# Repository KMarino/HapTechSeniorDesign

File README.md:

# HapTechSeniorDesign

#### Install dependencies

        sudo apt-get install build-essential scons cmake freeglut3-dev 

#### Rtaudio
First clone Rtaudio to extern
	cd extern/
	git clone https://github.com/thestk/rtaudio.git
	cd rtaudio
	autoconf
	./configure
	make
#### Aquila

First clone Aqulia to extern

	cd extern/
	git clone git://github.com/zsiciarz/aquila.git aquila-src
	cd ..

Make a build directory for Aquila
Aquila must be built with `cmake`, which doesn't play nice with `make`

        mkdir extern/aquila
	cd aquila
        cmake ../aquila-src
 	
	make
	sudo make install

#### Build Included dependencies

This will build gtest, jsoncpp, and aquila

### Build

        make

#### Run

        ./bin/effects_model_ui config/hardware.json config/mapping.json

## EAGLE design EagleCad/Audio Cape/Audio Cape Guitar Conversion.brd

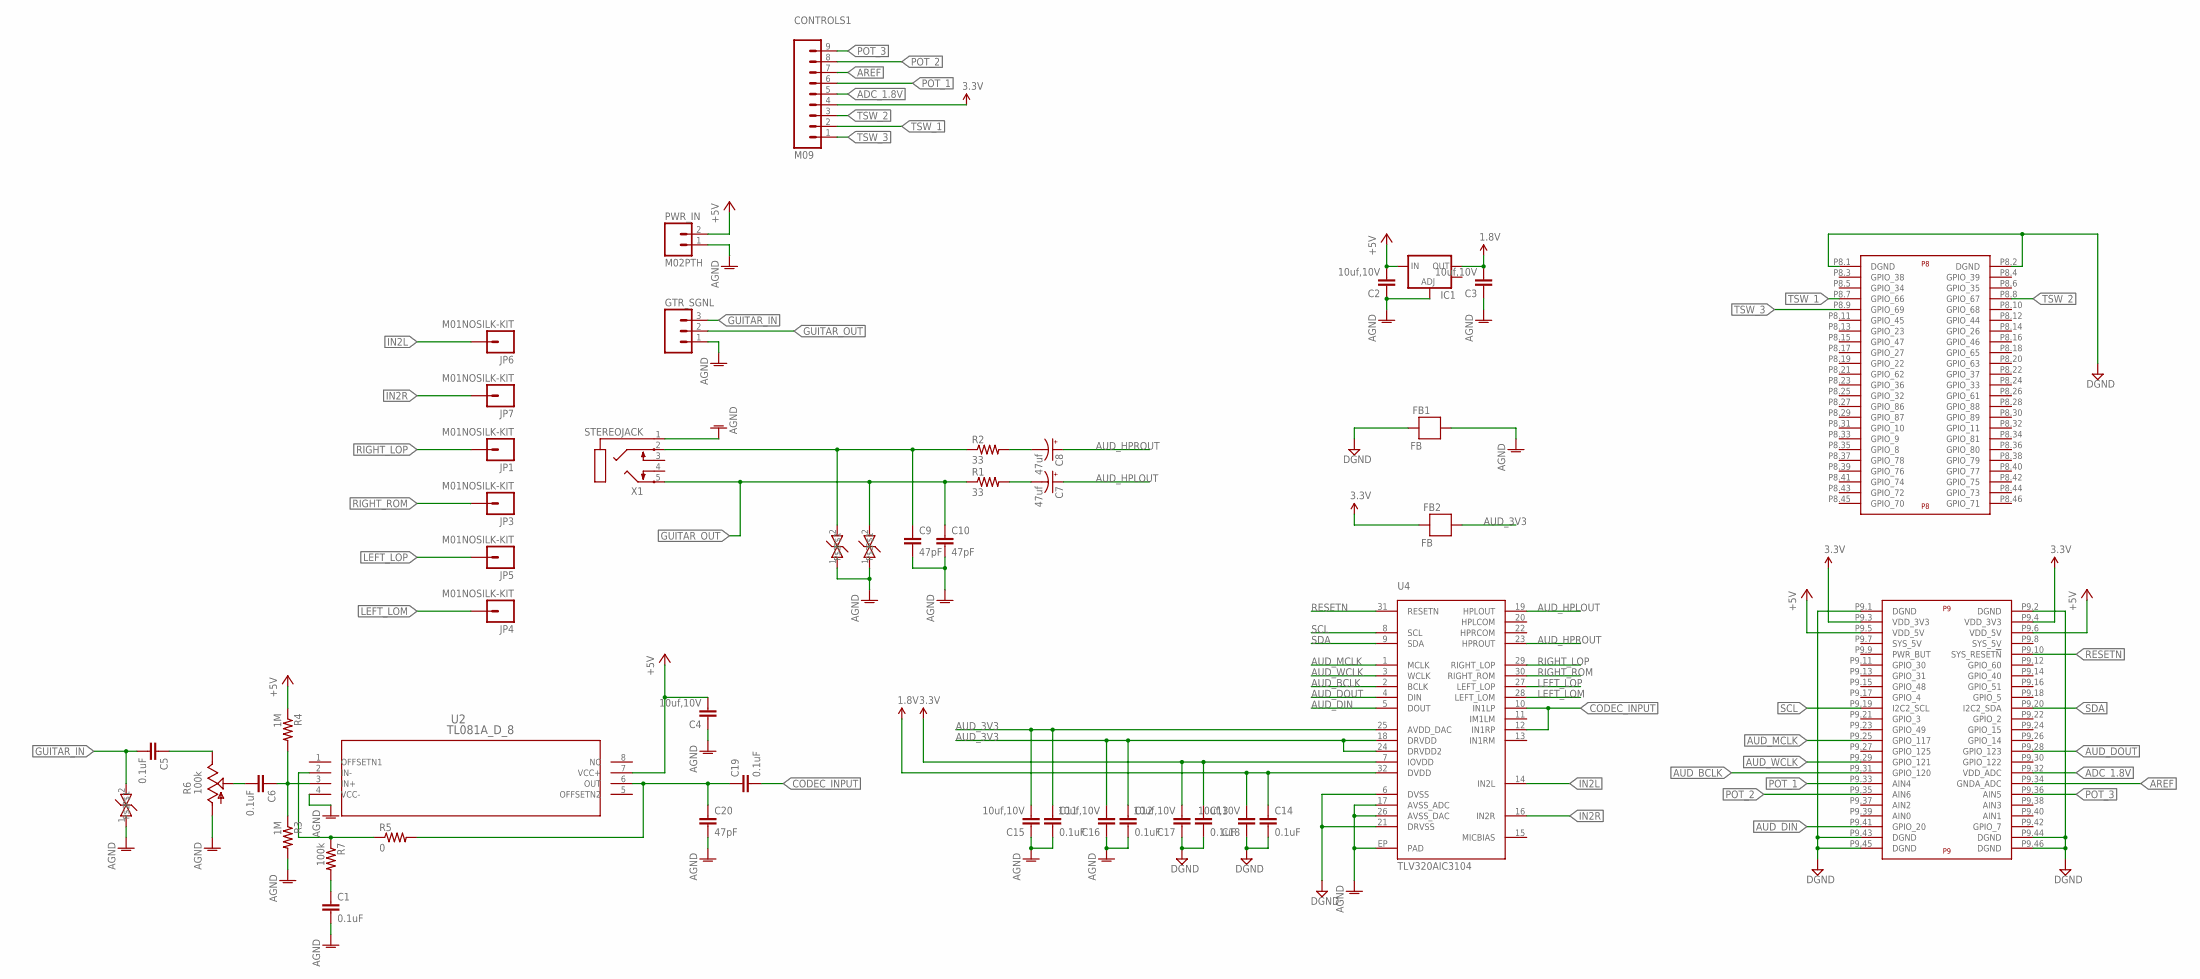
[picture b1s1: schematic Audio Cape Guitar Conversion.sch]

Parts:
C1, C5, C6, C11, C12, C13, C14, C19: 0.1uF; 0603-CAP
C2, C3, C4, C15, C16, C17, C18: 10uf,10V; 0603-CAP
C7, C8: 47uf; EIA3216
C9, C10, C20: 47pF; 0402-CAP
CONTROLS1: M09; 1X09
D1, D2, D3: PGB0010603MR; 0603
FB1, FB2: FB; 0603
GTR_SGNL: M03PTH; 1X03
IC1: V_REG_LM1117SOT223; SOT223
JP1, JP3, JP4, JP5, JP6, JP7: M01NOSILK-KIT; 1X01NS-KIT
PWR_IN: M02PTH; 1X02
R1, R2: 33; 1206
R3, R4: 1M; 1206
R5: 0; AXIAL-0.4
R6: 100k; S64Y
R7: 100k; 1206
U2: TL081A_D_8; D8
U4: TLV320AIC3104; QFN-32
U$1: BEAGLE_BONE_BLACK_CAPE
X1: STEREOJACK; STX3100

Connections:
1.8V: C3.2, C14.1, C18.2, IC1.2 (OUT), U4.32 (DVDD)
3.3V: C13.1, C17.2, CONTROLS1.4, FB2.2, U4.7 (IOVDD), U$1.P9.3 (VDD_3V3), U$1.P9.4 (VDD_3V3)
+5V: C2.2, C4.2, IC1.3 (IN), PWR_IN.2, R4.1, U2.7 (VCC+), U$1.P9.5 (VDD_5V), U$1.P9.6 (VDD_5V)
ADC_1.8V: CONTROLS1.5, U$1.P9.32 (VDD_ADC)
AGND: C1.2, C2.1, C3.1, C4.1, C9.2, C10.2, C11.2, C12.2, C15.1, C16.1, C20.2, D1.1, D2.1, D3.1, FB1.1, GTR_SGNL.1, IC1.1 (ADJ), PWR_IN.1, R3.2, R6.A, U2.4 (VCC-), U4.17 (AVSS_ADC), U4.26 (AVSS_DAC), U4.EP (PAD), X1.1
AREF: CONTROLS1.7, U$1.P9.34 (GNDA_ADC)
AUD_3V3: C11.1, C12.1, C15.2, C16.2, FB2.1, U4.18 (DRVDD), U4.24 (DRVDD2), U4.25 (AVDD_DAC)
AUD_BCLK: U4.2 (BCLK), U$1.P9.31 (GPIO_120)
AUD_DIN: U4.5 (DOUT), U$1.P9.41 (GPIO_20)
AUD_DOUT: U4.4 (DIN), U$1.P9.28 (GPIO_123)
AUD_HPLOUT: C7.A (+), U4.19 (HPLOUT)
AUD_HPROUT: C8.A (+), U4.23 (HPROUT)
AUD_MCLK: U4.1 (MCLK), U$1.P9.25 (GPIO_117)
AUD_WCLK: U4.3 (WCLK), U$1.P9.29 (GPIO_121)
CODEC_INPUT: C19.2, U4.10 (IN1LP), U4.12 (IN1RP)
DGND: C13.2, C14.2, C17.1, C18.1, FB1.2, U4.6 (DVSS), U4.21 (DRVSS), U$1.P8.1 (DGND), U$1.P8.2 (DGND), U$1.P9.1 (DGND), U$1.P9.2 (DGND), U$1.P9.43 (DGND), U$1.P9.44 (DGND), U$1.P9.45 (DGND), U$1.P9.46 (DGND)
GUITAR_IN: C5.2, D3.2, GTR_SGNL.3
GUITAR_OUT: C10.1, D2.2, GTR_SGNL.2, R1.1, X1.5
IN2L: JP6.1, U4.14 (IN2L)
IN2R: JP7.1, U4.16 (IN2R)
LEFT_LOM: JP4.1, U4.28 (LEFT_LOM)
LEFT_LOP: JP5.1, U4.27 (LEFT_LOP)
unnamed: C7.C (-), R1.2
unnamed: C5.1, R6.E
unnamed: C6.1, R3.1, R4.2, U2.3 (IN+)
unnamed: C1.1, R7.2
unnamed: C8.C (-), R2.2
unnamed: R5.P$1 (1), R7.1, U2.2 (IN-)
unnamed: C19.1, C20.1, R5.P$2 (2), U2.6 (OUT)
unnamed: C6.2, R6.S
OUTR: C9.1, D1.2, R2.1, X1.2
POT_1: CONTROLS1.6, U$1.P9.33 (AIN4)
POT_2: CONTROLS1.8, U$1.P9.35 (AIN6)
POT_3: CONTROLS1.9, U$1.P9.36 (AIN5)
RESETN: U4.31 (RESETN), U$1.P9.10 (SYS_RESET!N)
RIGHT_LOP: JP1.1, U4.29 (RIGHT_LOP)
RIGHT_ROM: JP3.1, U4.30 (RIGHT_ROM)
SCL: U4.8 (SCL), U$1.P9.19 (I2C2_SCL)
SDA: U4.9 (SDA), U$1.P9.20 (I2C2_SDA)
TSW_1: CONTROLS1.2, U$1.P8.7 (GPIO_66)
TSW_2: CONTROLS1.3, U$1.P8.8 (GPIO_67)
TSW_3: CONTROLS1.1, U$1.P8.9 (GPIO_69)

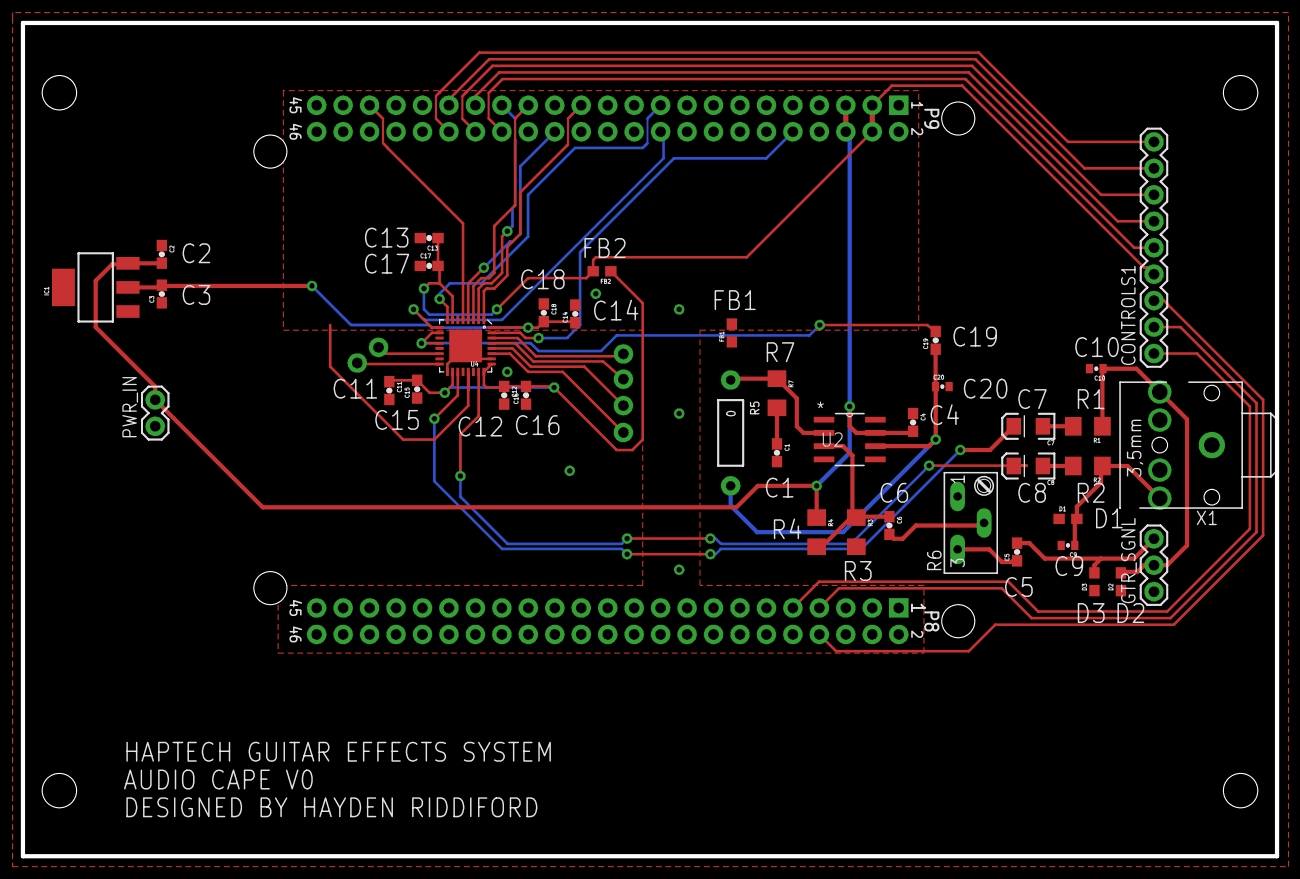
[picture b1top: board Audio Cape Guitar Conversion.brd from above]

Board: 2 copper layers, 120.4 x 80.0 mm, 46 parts (0 on the bottom side), 42 nets.

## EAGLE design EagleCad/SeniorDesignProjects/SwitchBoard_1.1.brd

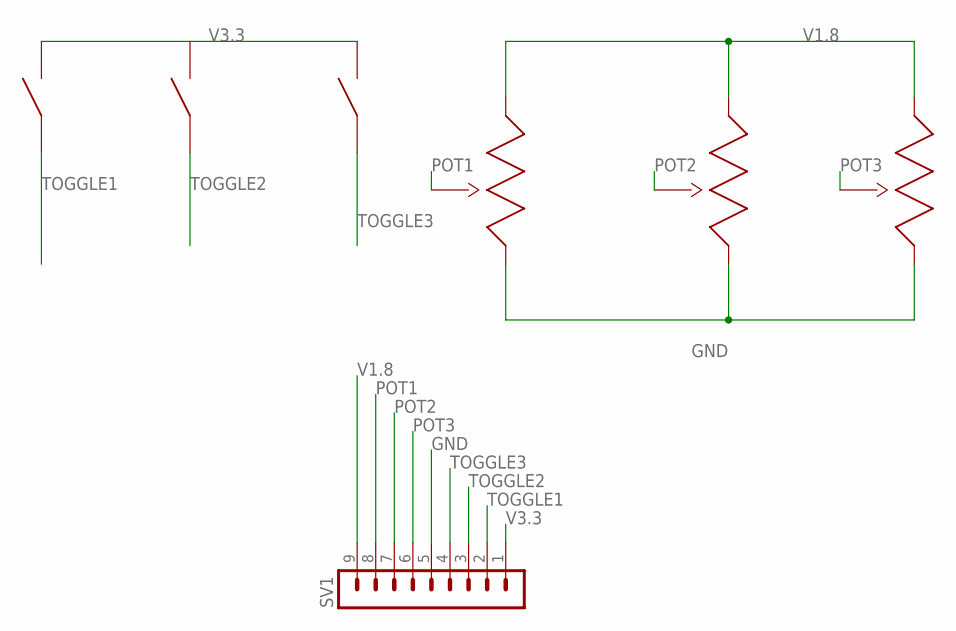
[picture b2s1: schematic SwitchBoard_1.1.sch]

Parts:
POT1, POT2, POT3: PRS11S-11; POT-SMD
SV1: MA09-1
TOGGLE1, TOGGLE2, TOGGLE3: COM-09276; SPST-TOGGLE-SWITCH

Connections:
GND: POT1.1, POT2.1, POT3.1, SV1.5
POT1: POT1.2, SV1.8
POT2: POT2.2, SV1.7
POT3: POT3.2, SV1.6
TOGGLE1: SV1.2, TOGGLE1.1
TOGGLE2: SV1.3, TOGGLE2.1
TOGGLE3: SV1.4, TOGGLE3.1
V1.8: POT1.3, POT2.3, POT3.3, SV1.9
V3.3: SV1.1, TOGGLE1.2, TOGGLE2.2, TOGGLE3.2

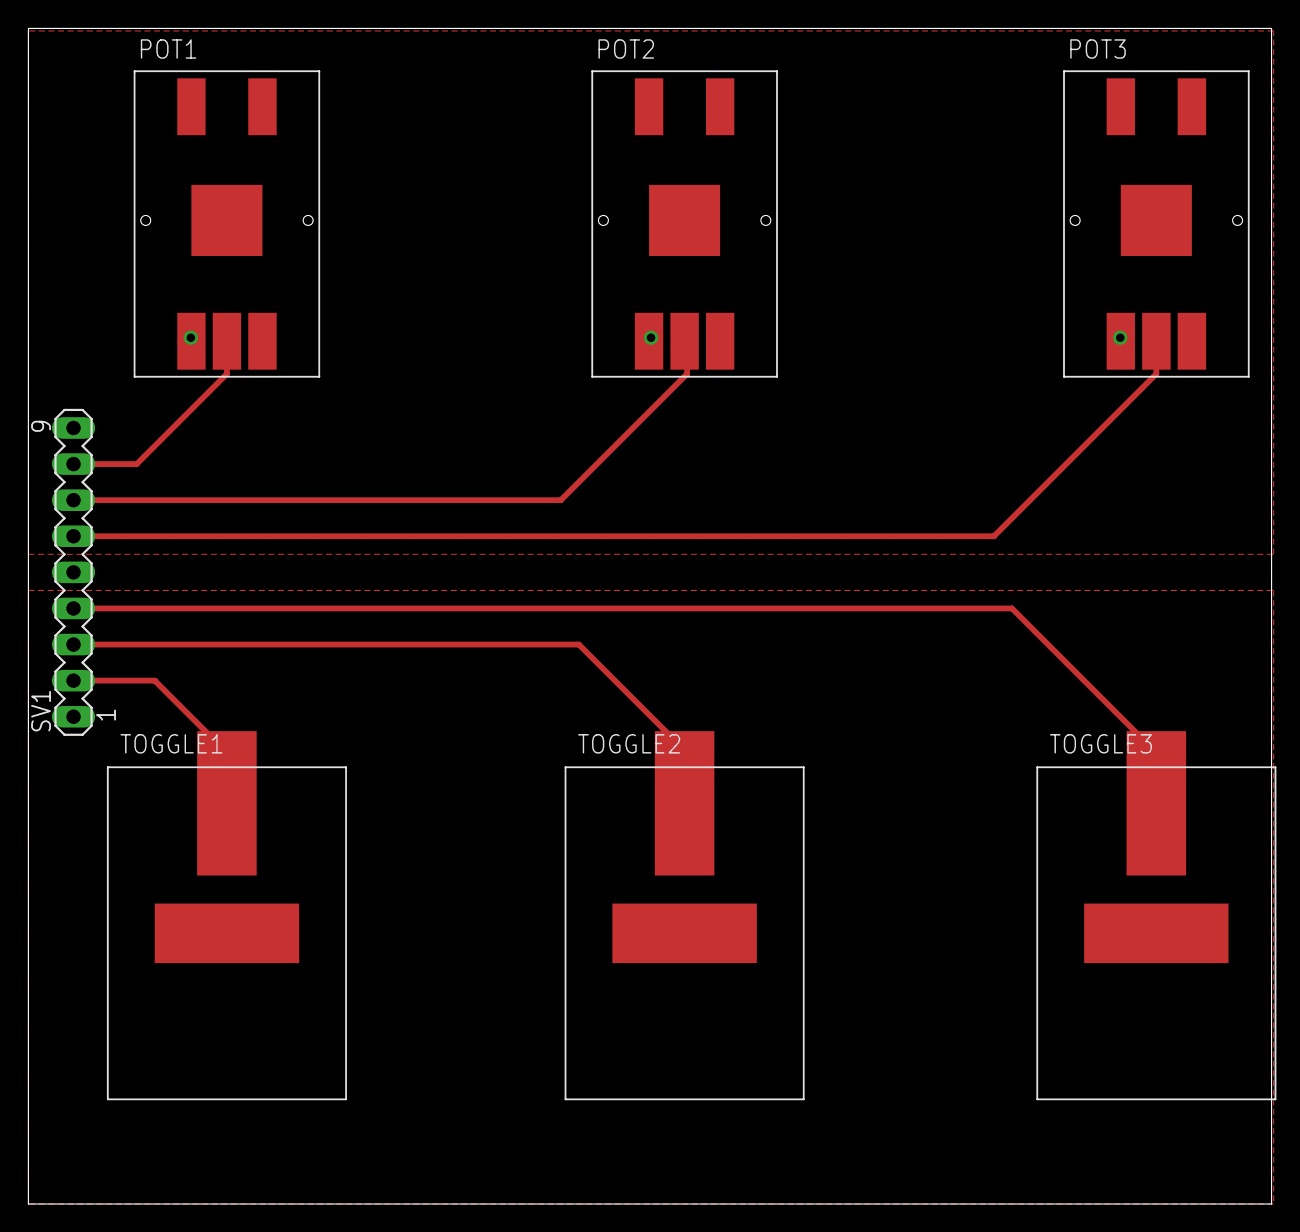
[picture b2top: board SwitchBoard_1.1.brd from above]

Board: 2 copper layers, 87.5 x 82.7 mm, 7 parts (0 on the bottom side), 9 nets.

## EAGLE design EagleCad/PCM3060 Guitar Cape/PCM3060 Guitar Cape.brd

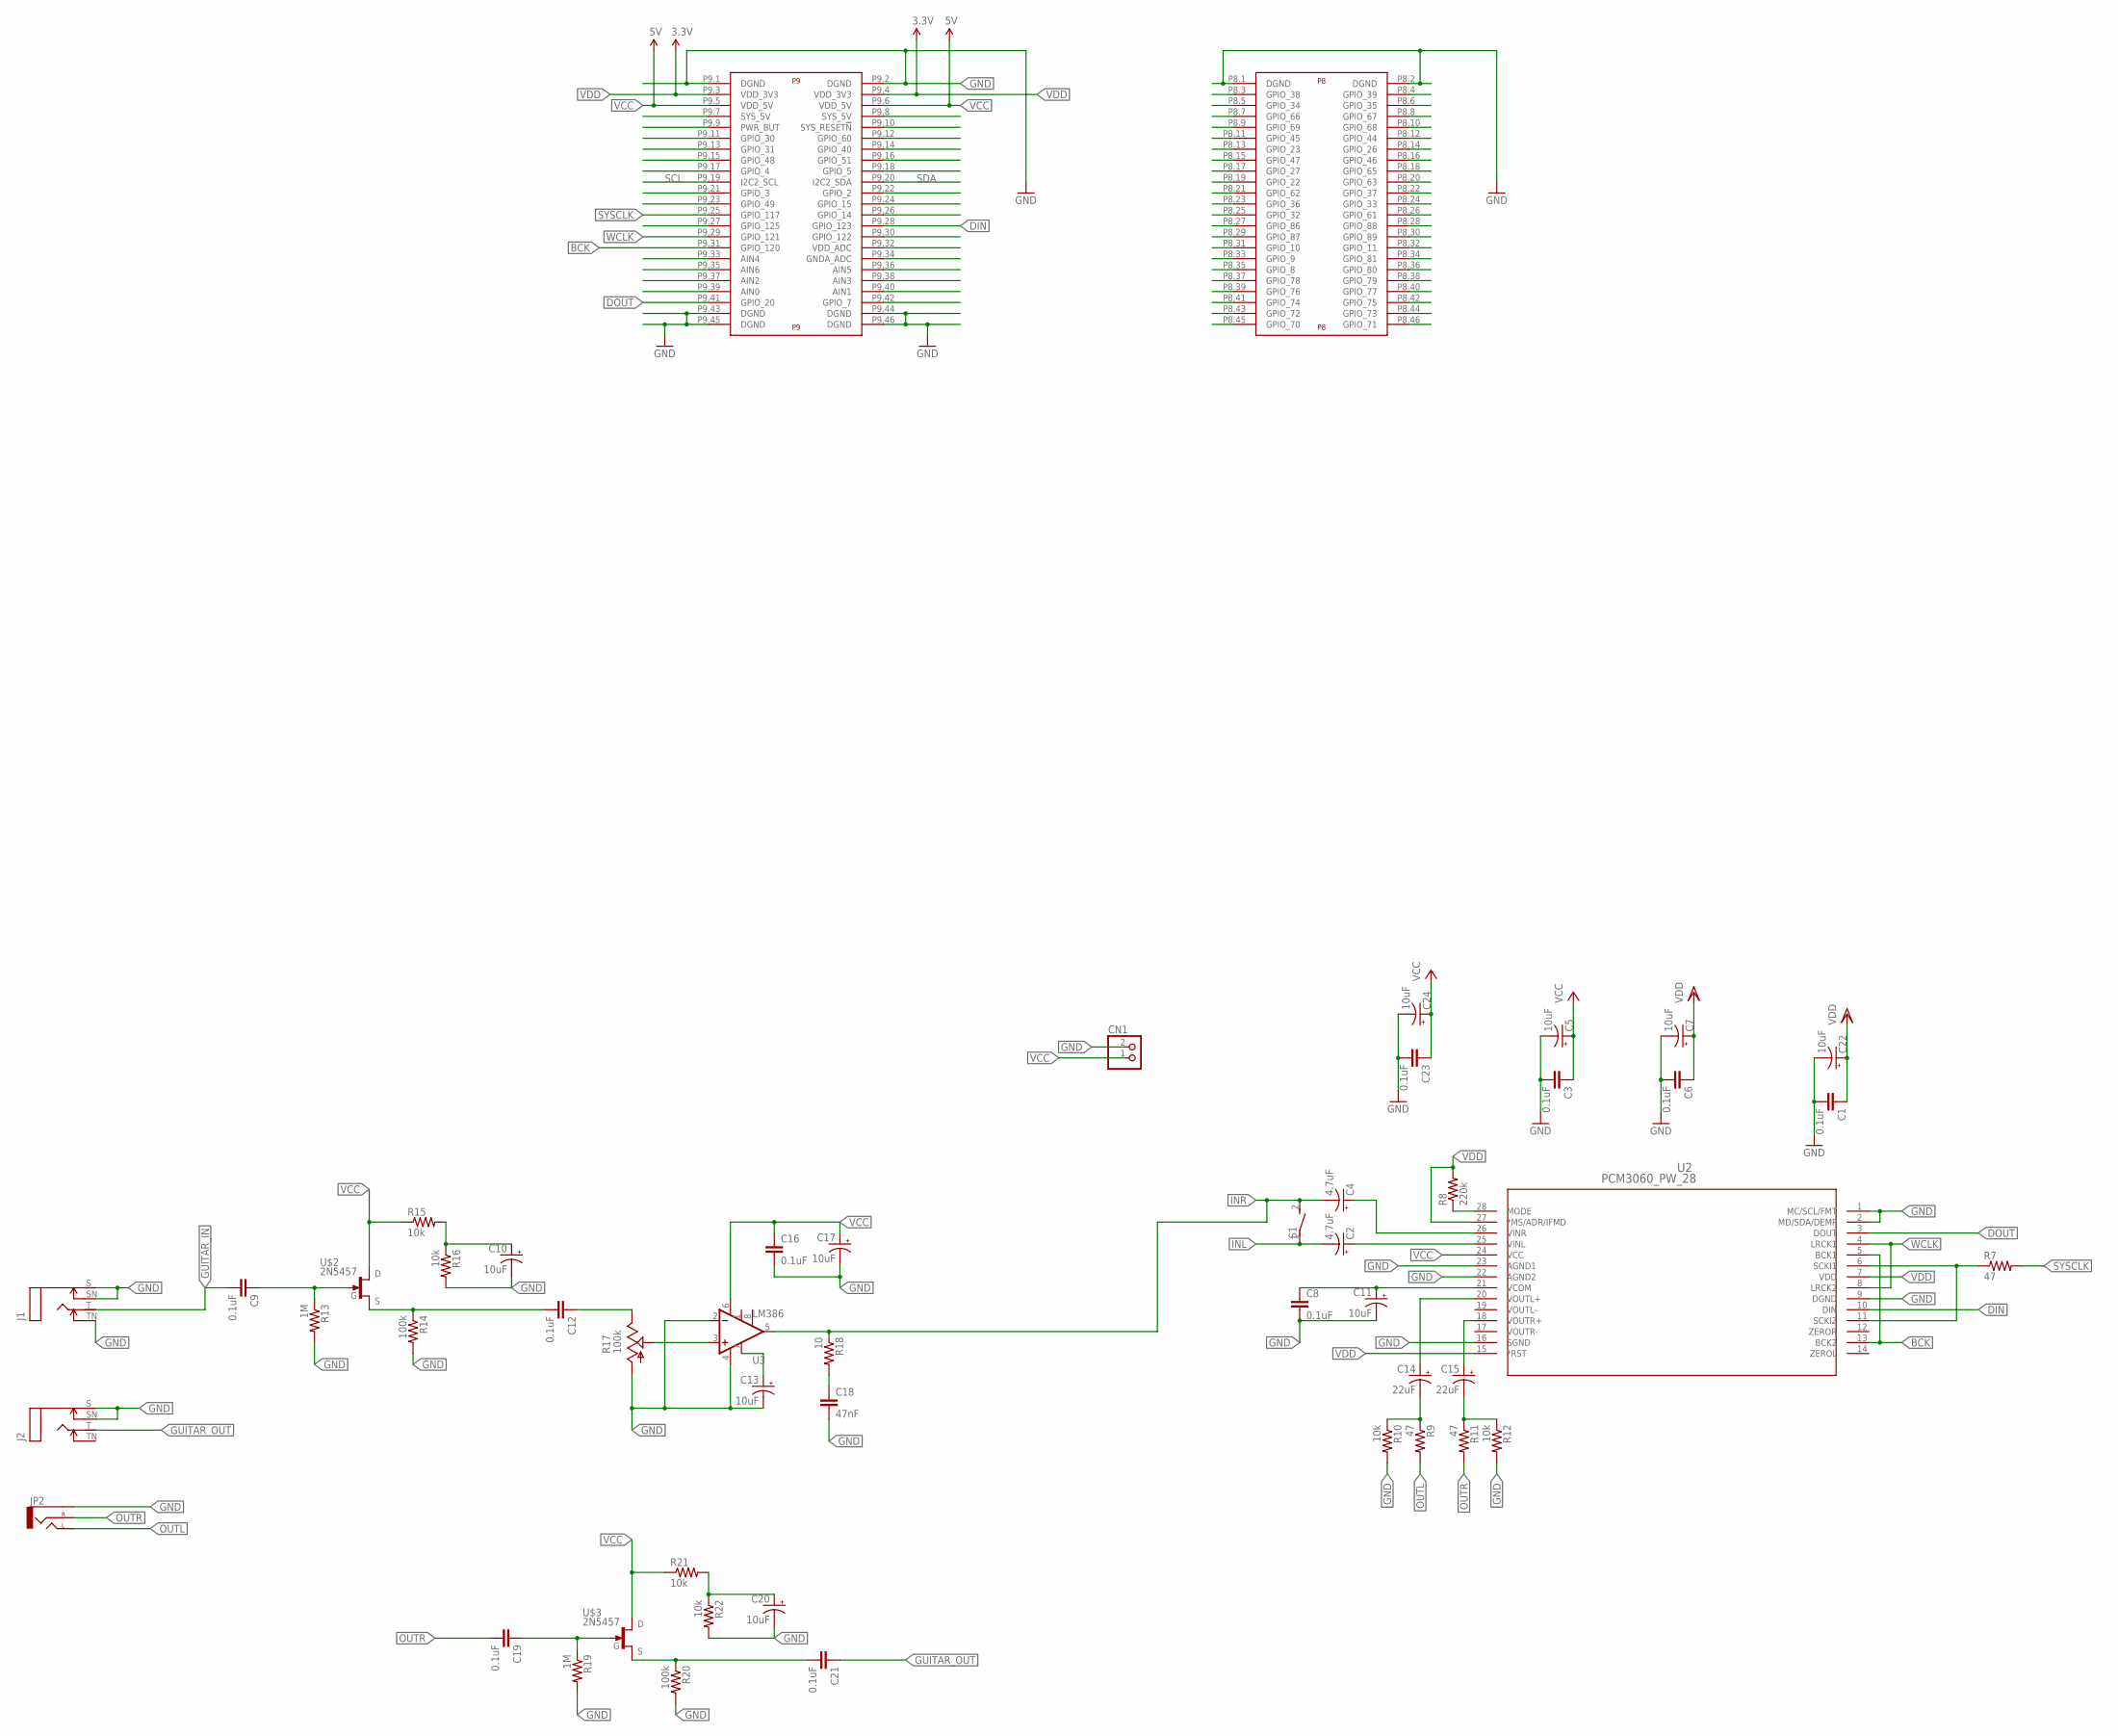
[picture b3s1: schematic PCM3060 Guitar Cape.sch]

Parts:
C1, C3, C6, C8, C9, C12, C16, C19, C21, C23: 0.1uF; 0603-CAP
C2, C4: 4.7uF; CPOL-RADIAL-10UF-25V
C5, C7, C10, C11, C13, C17, C20, C22, C24: 10uF; CPOL-RADIAL-10UF-25V
C14, C15: 22uF; CPOL-RADIAL-10UF-25V
C18: 47nF; 0603-CAP
CN1: JST_2PIN-THM; JST-PH-2-THM
J1, J2: MONOSW; NMJ4HCD2
JP2: AUDIO-JACK2.5MM; STEREOJACK2.5MM_STEREOJACK2.5MM
R7, R9, R11: 47; 1206
R8: 220k; 1206
R10, R12, R15, R16, R21, R22: 10k; 1206
R13, R19: 1M; 1206
R14, R20: 100k; 1206
R17: 100k; RJ9W
R18: 10; 1206
S1: DS01E; DS-01
U2: PCM3060_PW_28; PW28
U3: LM386; DIP08
U$1: BEAGLE_BONE_BLACK_CAPE
U$2, U$3: 2N5457; TO-92

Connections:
BCK: U2.5 (BCK1), U2.13 (BCK2), U$1.P9.31 (GPIO_120)
DIN: U2.10 (DIN), U$1.P9.28 (GPIO_123)
DOUT: U2.3 (DOUT), U$1.P9.41 (GPIO_20)
GND: C1.2, C3.2, C5.2 (-), C6.2, C7.2 (-), C8.2, C10.2 (-), C11.2 (-), C13.2 (-), C16.2, C17.2 (-), C18.2, C20.2 (-), C22.2 (-), C23.2, C24.2 (-), CN1.2 (1), J1.S, J1.SN, J1.TN, J2.S, J2.SN, JP2.RING1 (SLEEVE), R10.2, R12.2, R13.2, R14.2, R16.2, R17.A, R19.2, R20.2, R22.2, U2.1 (MC/SCL/FMT), U2.2 (MD/SDA/DEMP), U2.9 (DGND), U2.16 (SGND), U2.22 (AGND2), U2.23 (AGND1), U3.2 (-IN), U3.4 (V-), U$1.P8.1 (DGND), U$1.P8.2 (DGND), U$1.P9.1 (DGND), U$1.P9.2 (DGND), U$1.P9.43 (DGND), U$1.P9.44 (DGND), U$1.P9.45 (DGND), U$1.P9.46 (DGND)
GUITAR_IN: C9.2, J1.T
GUITAR_OUT: C21.1, J2.T
INL: C2.2 (-), S1.1
INR: C4.2 (-), R18.1, S1.2, U3.5 (OUT)
unnamed: C2.1 (+), U2.25 (VINL)
unnamed: R7.1, U2.6 (SCKI1), U2.11 (SCKI2)
unnamed: C8.1, C11.1 (+), U2.21 (VCOM)
unnamed: R8.1, U2.28 (MODE)
unnamed: C4.1 (+), U2.26 (VINR)
unnamed: C14.1 (+), U2.20 (VOUTL+)
unnamed: C15.1 (+), U2.18 (VOUTR+)
unnamed: C14.2 (-), R9.1, R10.1
unnamed: C15.2 (-), R11.1, R12.1
unnamed: C9.1, R13.1, U$2.3 (G)
unnamed: C12.2, R14.1, U$2.2 (S)
unnamed: C10.1 (+), R15.2, R16.1
unnamed: R17.S, U3.3 (+IN)
unnamed: C13.1 (+), U3.7 (BP)
unnamed: C18.1, R18.2
unnamed: C12.1, R17.E
unnamed: C19.1, R19.1, U$3.3 (G)
unnamed: C21.2, R20.1, U$3.2 (S)
unnamed: C20.1 (+), R21.2, R22.1
OUTL: JP2.SHIELD (LEFT), R9.2
OUTR: C19.2, JP2.TIP (RIGHT), R11.2
SCL: U$1.P9.19 (I2C2_SCL)
SDA: U$1.P9.20 (I2C2_SDA)
SYSCLK: R7.2, U$1.P9.25 (GPIO_117)
VCC: C3.1, C5.1 (+), C16.1, C17.1 (+), C23.1, C24.1 (+), CN1.1 (2), R15.1, R21.1, U2.24 (VCC), U3.6 (V+), U$1.P9.5 (VDD_5V), U$1.P9.6 (VDD_5V), U$2.1 (D), U$3.1 (D)
VDD: C1.1, C6.1, C7.1 (+), C22.1 (+), R8.2, U2.7 (VDD), U2.15 (*RST), U2.27 (*MS/ADR/IFMD), U$1.P9.3 (VDD_3V3), U$1.P9.4 (VDD_3V3)
WCLK: U2.4 (LRCK1), U2.8 (LRCK2), U$1.P9.29 (GPIO_121)

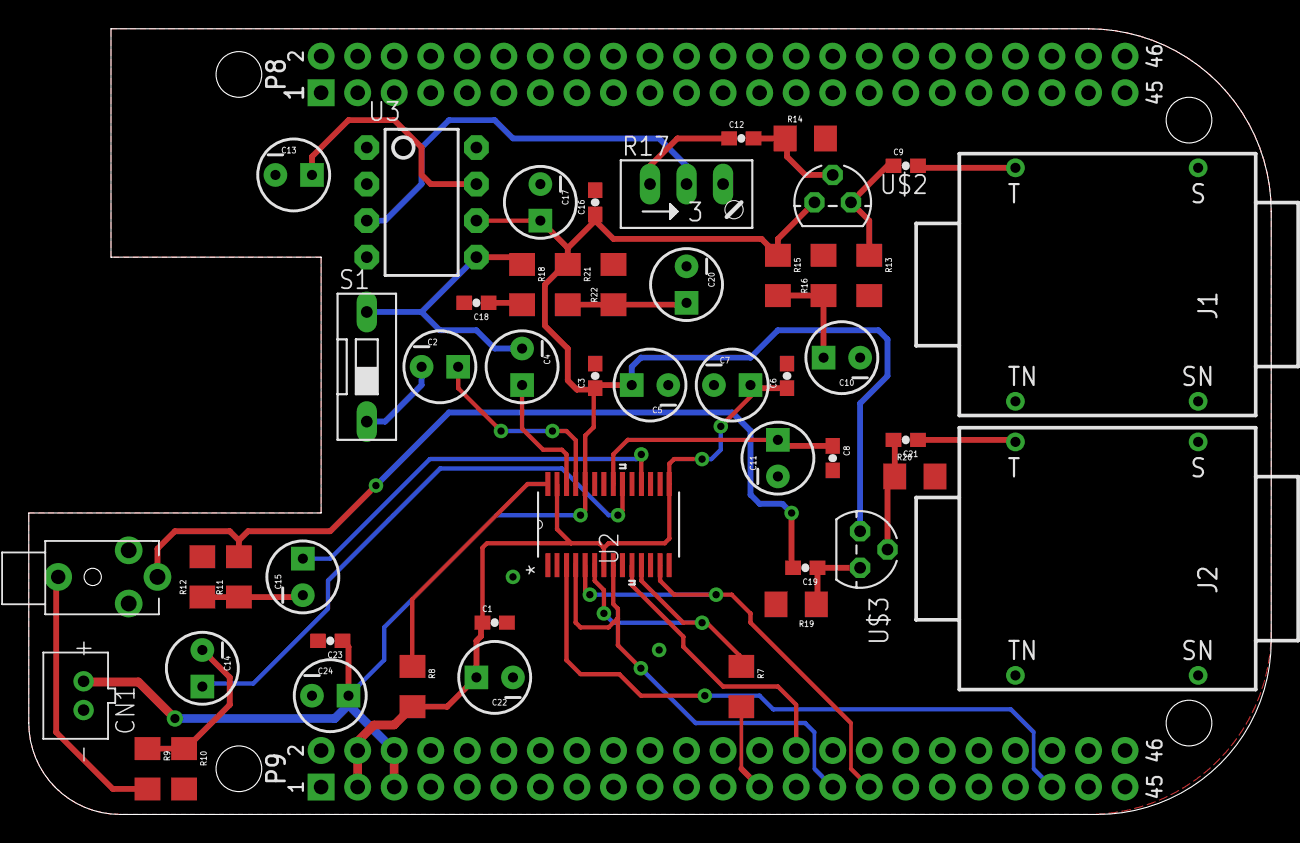
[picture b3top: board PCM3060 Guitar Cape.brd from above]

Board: 2 copper layers, 86.4 x 54.6 mm, 50 parts (0 on the bottom side), 33 nets.

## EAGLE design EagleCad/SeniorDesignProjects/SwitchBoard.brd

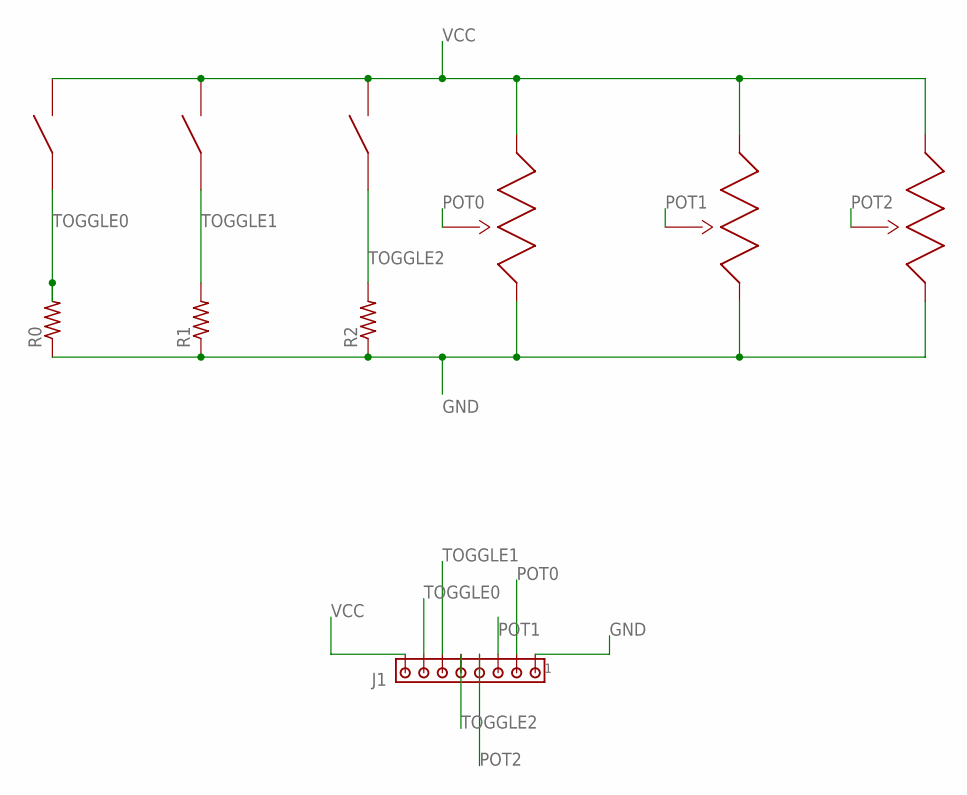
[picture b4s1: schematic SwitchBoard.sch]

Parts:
J1: MTA08-100; 10X08MTA
POT0, POT1, POT2: PRS11S-11; POT-SMD
R0, R1, R2: R-US_0204/5; 0204/5
TOGGLE0, TOGGLE1, TOGGLE2: COM-09276; SPST-TOGGLE-SWITCH

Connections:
GND: J1.1, POT0.1, POT1.1, POT2.1, R0.1, R1.1, R2.1
POT0: J1.2, POT0.2
POT1: J1.3, POT1.2
POT2: J1.4, POT2.2
TOGGLE0: J1.7, R0.2, TOGGLE0.1
TOGGLE1: J1.6, R1.2, TOGGLE1.1
TOGGLE2: J1.5, R2.2, TOGGLE2.1
VCC: J1.8, POT0.3, POT1.3, POT2.3, TOGGLE0.2, TOGGLE1.2, TOGGLE2.2

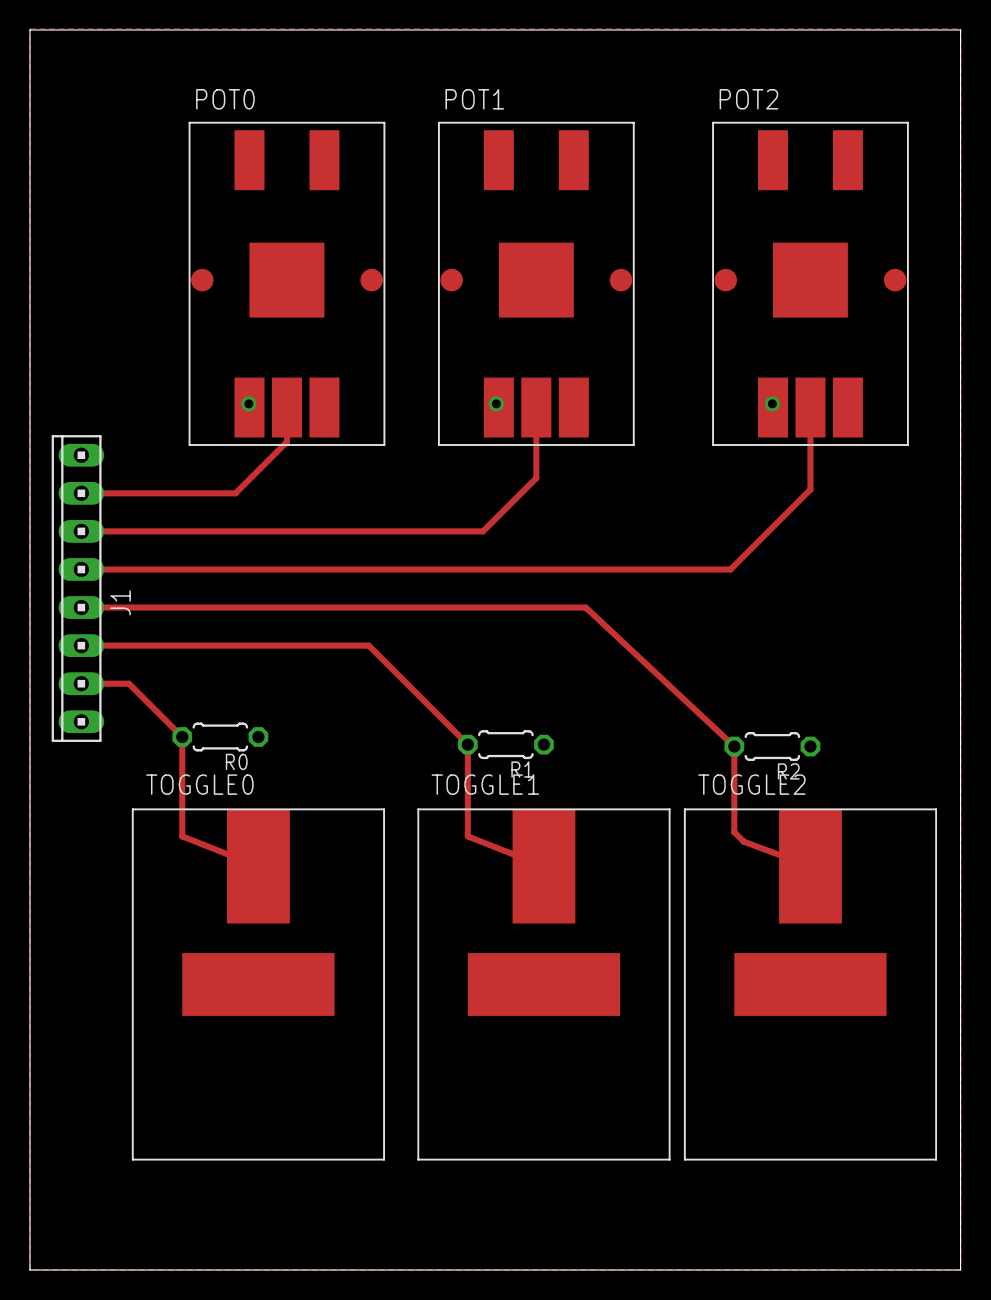
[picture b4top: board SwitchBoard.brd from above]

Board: 2 copper layers, 62.1 x 82.7 mm, 10 parts (0 on the bottom side), 8 nets.

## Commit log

2015-01-11 Initial commit. Set up unittest and json libraries, put help on installing in README, added gitignore, set up Makefile with exaples from last project I did
2015-01-11 Added json file reading basics, code stub for EffectsModel
2015-01-11 Renamed some files, added more class and function stubs, created a main file, updated README to link everything correctly
2015-01-19 Added a bunch fo new classes for effects. Also tested to make sure serialization of effects works correctly
2015-01-20 Added message update stuff. Not sure if it actually is correct yet. Will test this for real, but it doesn't cause a compile issue, so there's that
2015-01-25 Updated README for OpenGL
2015-01-25 Finished serialization functions for messages. Also made unit tests to make sure everything actually works
2015-02-02 Made parsing for hardware config file
2015-02-04 got opengl to display circle on screen
2015-02-11 Fixed hardware state config, reading and storage to be a bit more sensible
2015-02-11 Added linking for opengl to makefile
2015-02-11 Created Folders for EagleCad Libraries, Schematics, and Boards
2015-02-12 Finished Switch Board schematic and Board layout
2015-02-13 Fixed Toggle Switch package for board layout
2015-02-21 Make the dot move
2015-02-22 made the dot move. with the mouse. it's pretty sweet.
2015-02-22 Added code for both config files to be read and interpreted
2015-02-24 PCM3060 Guitar Cape
    Designed a cape to input/output guitar signal according to proposed
    design. May change depending on pending hardware testing.
2015-02-24 Fixed Grounding Issue on Output Jack
    Previously, the switched 1/4" output jack for the system would be
    grounded when no cable was connected. This is correct for the input,
    however grounding the output of the system is not proper.
2015-03-01 Added code to effectsmodel to receive updates from main program, update dial switches and send messages to DSP program. Still needs to actually read the values from pins and actually send messages to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
2015-03-01 Forgot to save a file. Should all be okay now
2015-03-01 Uses eventinfo class, generics
2015-03-01 Flipped x and y. X is now index 0 and Y is index 1, which just makes way more sense
2015-03-01 cleaned up directions
2015-03-01 fixed 'undefined reference to symbol 'pthread_key_delete@@GLIBC_2.2.5' issue
2015-03-01 ignoring some compiled files
2015-03-01 hmmm
2015-03-01 missed some things in the readme
2015-03-01 added EffectsModel and close function
2015-03-01 deleting objects on exit
2015-03-01 Added accessors to EffectUpdateMessage so DSP can actually read what's in it
2015-03-01 added timer func
2015-03-01 Added accessor in EffectsModel to get the screen width and height
2015-03-01 fixed bugs with modelaccess
2015-03-01 added bin dir
2015-03-01 committing broken for Kenny to fix, profile.cpp line 80 count func
2015-03-01 Fixed error in effectsmodel where it doesn't set to value from the wind
2015-03-01 cleaned up effects_model_ui
2015-03-01 aquila things
2015-03-01 updated makefile to use local jsoncpp
2015-03-01 fixed aquila directory
2015-03-01 removed aquila-src
2015-03-01 created module
2015-03-01 added module for real
2015-03-01 fixed for real
2015-03-01 added deps make task
2015-03-01 removed compiled aquila from repo
2015-03-01 some Makefile refactor
2015-03-01 updated to match makefile changes
2015-03-01 clarity
2015-03-06 added working device tree overlay for modded cape
2015-03-06 added test file (30s sweep)
2015-03-09 Updated sch and brd files. Spaced out components, seperated ADC and GPIO power
2015-03-09 minor update the toggle switch footprint to allow for easier soldering
2015-03-10 fixed aquila stuff
2015-03-10 minor fix in readme, fullscreen with q to quit and cutdown events in effects_ui
2015-03-10 fixed duplicate code
2015-03-14 Gitignore merge
2015-03-15 Added a ton of verification. All code should be verified to a reasonable degree except for EffectsModel. That code is hopefully more straightforward. Will be able to write a better unittest for that 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
2015-03-26 cleanup
2015-03-26 added some useful bbb files
2015-03-26 moved some files around
2015-03-26 removed submodule
2015-03-26 fixed aquila paths
2015-03-26 fixed misnamed make task
2015-03-26 updated readme for changes
2015-03-26 made make get-deps task
2015-03-26 updated readme for new task
2015-03-26 added Travis.yml for free CI :)
2015-03-26 removed gitmodules
2015-03-26 wrong file name
2015-03-28 DTOs and scripts to add to beaglebone, basic C functions to read the IO
2015-03-28 Fixed ambgious absolute value call in unittest
2015-03-28 Fixed aquila instructions again
2015-03-28 fixed pthreads bug in Makefile
2015-03-28 Fixed dsp make in Makefile
2015-03-28 fixed unittesting.cpp for 0 test
2015-03-28 fixed formatting
2015-03-29 Added h and cpp files for IPC sockets. not integrated yet
2015-03-29 forgot one
2015-03-29 Fixed stream/dgram errors in socket things. Also minor change in effectsmodel for usability of var
2015-04-03 Audio Cape with Guitar Preamp
    Updated cape that includes the codec for signal conversion, as well as a
    preamp for the guitar input. Headers for power, guitar signal
    input/output, and signals routed to the controls board are also included
    on the board.
2015-04-04 Integrating socket code with minor improvements
2015-04-04 made socket test
2015-04-04 integrating ipc code and test
2015-04-04 Integrated gpio code into main build. Also changed functions slightly so it returns either 0 or 1 or it returns a float voltage value
2015-04-04 pthreads in socket code. doesn't work yet.
2015-04-05 Unreverted a lot of things. Added GPIO back in and fixed the original bug. Should now be able to read from hardware pins
2015-04-05 dsp code, still has threading issues but runs
2015-04-05 Fixed IPC with test and all using unlink
2015-04-05 Added test executable that displays the key presses so we can update the config file
2015-04-05 Changed keypress values in config to be integer type since they may not be representable characters on the keyboard
2015-04-06 Adding IPC receive to DSP file
2015-04-06 Let's not make a new server indefinitely
2015-04-09 built more of the framework for dsp, still no functionality yet
2015-04-09 Added testing file for GPIO. Need to test that it actually works
2015-04-14 Added new config files that will let us test the simpler functions.
2015-04-16 SFML update instructions
2015-04-16 Kenny changed print statements and now eveything works
2015-04-16 fixed bbb readme
2015-04-18 Trying to rewrite graphics in gl not glut for faster perf
2015-04-18 display var
2015-04-18 updated run script to correct path
2015-04-18 fixed kenny's silly copy pasta mistake
2015-04-19 Added a comment to the json file for the arrow key thing
2015-04-19 Tested arrow key fix with the key_test test executable
2015-04-19 Added testbed for dsp program that doesn't require touchscreen overhead
2015-04-20 Kenny can't see my push...
2015-04-20 Updated pin read changes to hopefully solve file read issue
2015-04-22 Basic passthrough built into project
2015-04-22 Full Passthrough built into project, also, kenny rebuild your scons with gcc 4.9.2 so we can have a unified folder to point at
2015-04-23 non building code, resynching
2015-04-23 IPC testing needed
2015-04-23 last minute refactoring to get around sockets not working atm
2015-04-23 and associated make
2015-04-23 headers would be helpful too I suppose
2015-04-23 fucking with header linking
2015-04-23 model updates
2015-04-26 Code used in demo
2015-04-26 Should put distortion on pat
2015-04-27 modified dtsScript to work with current image

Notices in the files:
parts and their libraries:
SparkFun-Boards: Licensing: CC v3.0 Share-Alike You are welcome to use this library for commercial purposes.
SparkFun-Connectors: Licensing: Creative Commons ShareAlike 4.0 International - https://creativecommons.org/licenses/by-sa/4.0
